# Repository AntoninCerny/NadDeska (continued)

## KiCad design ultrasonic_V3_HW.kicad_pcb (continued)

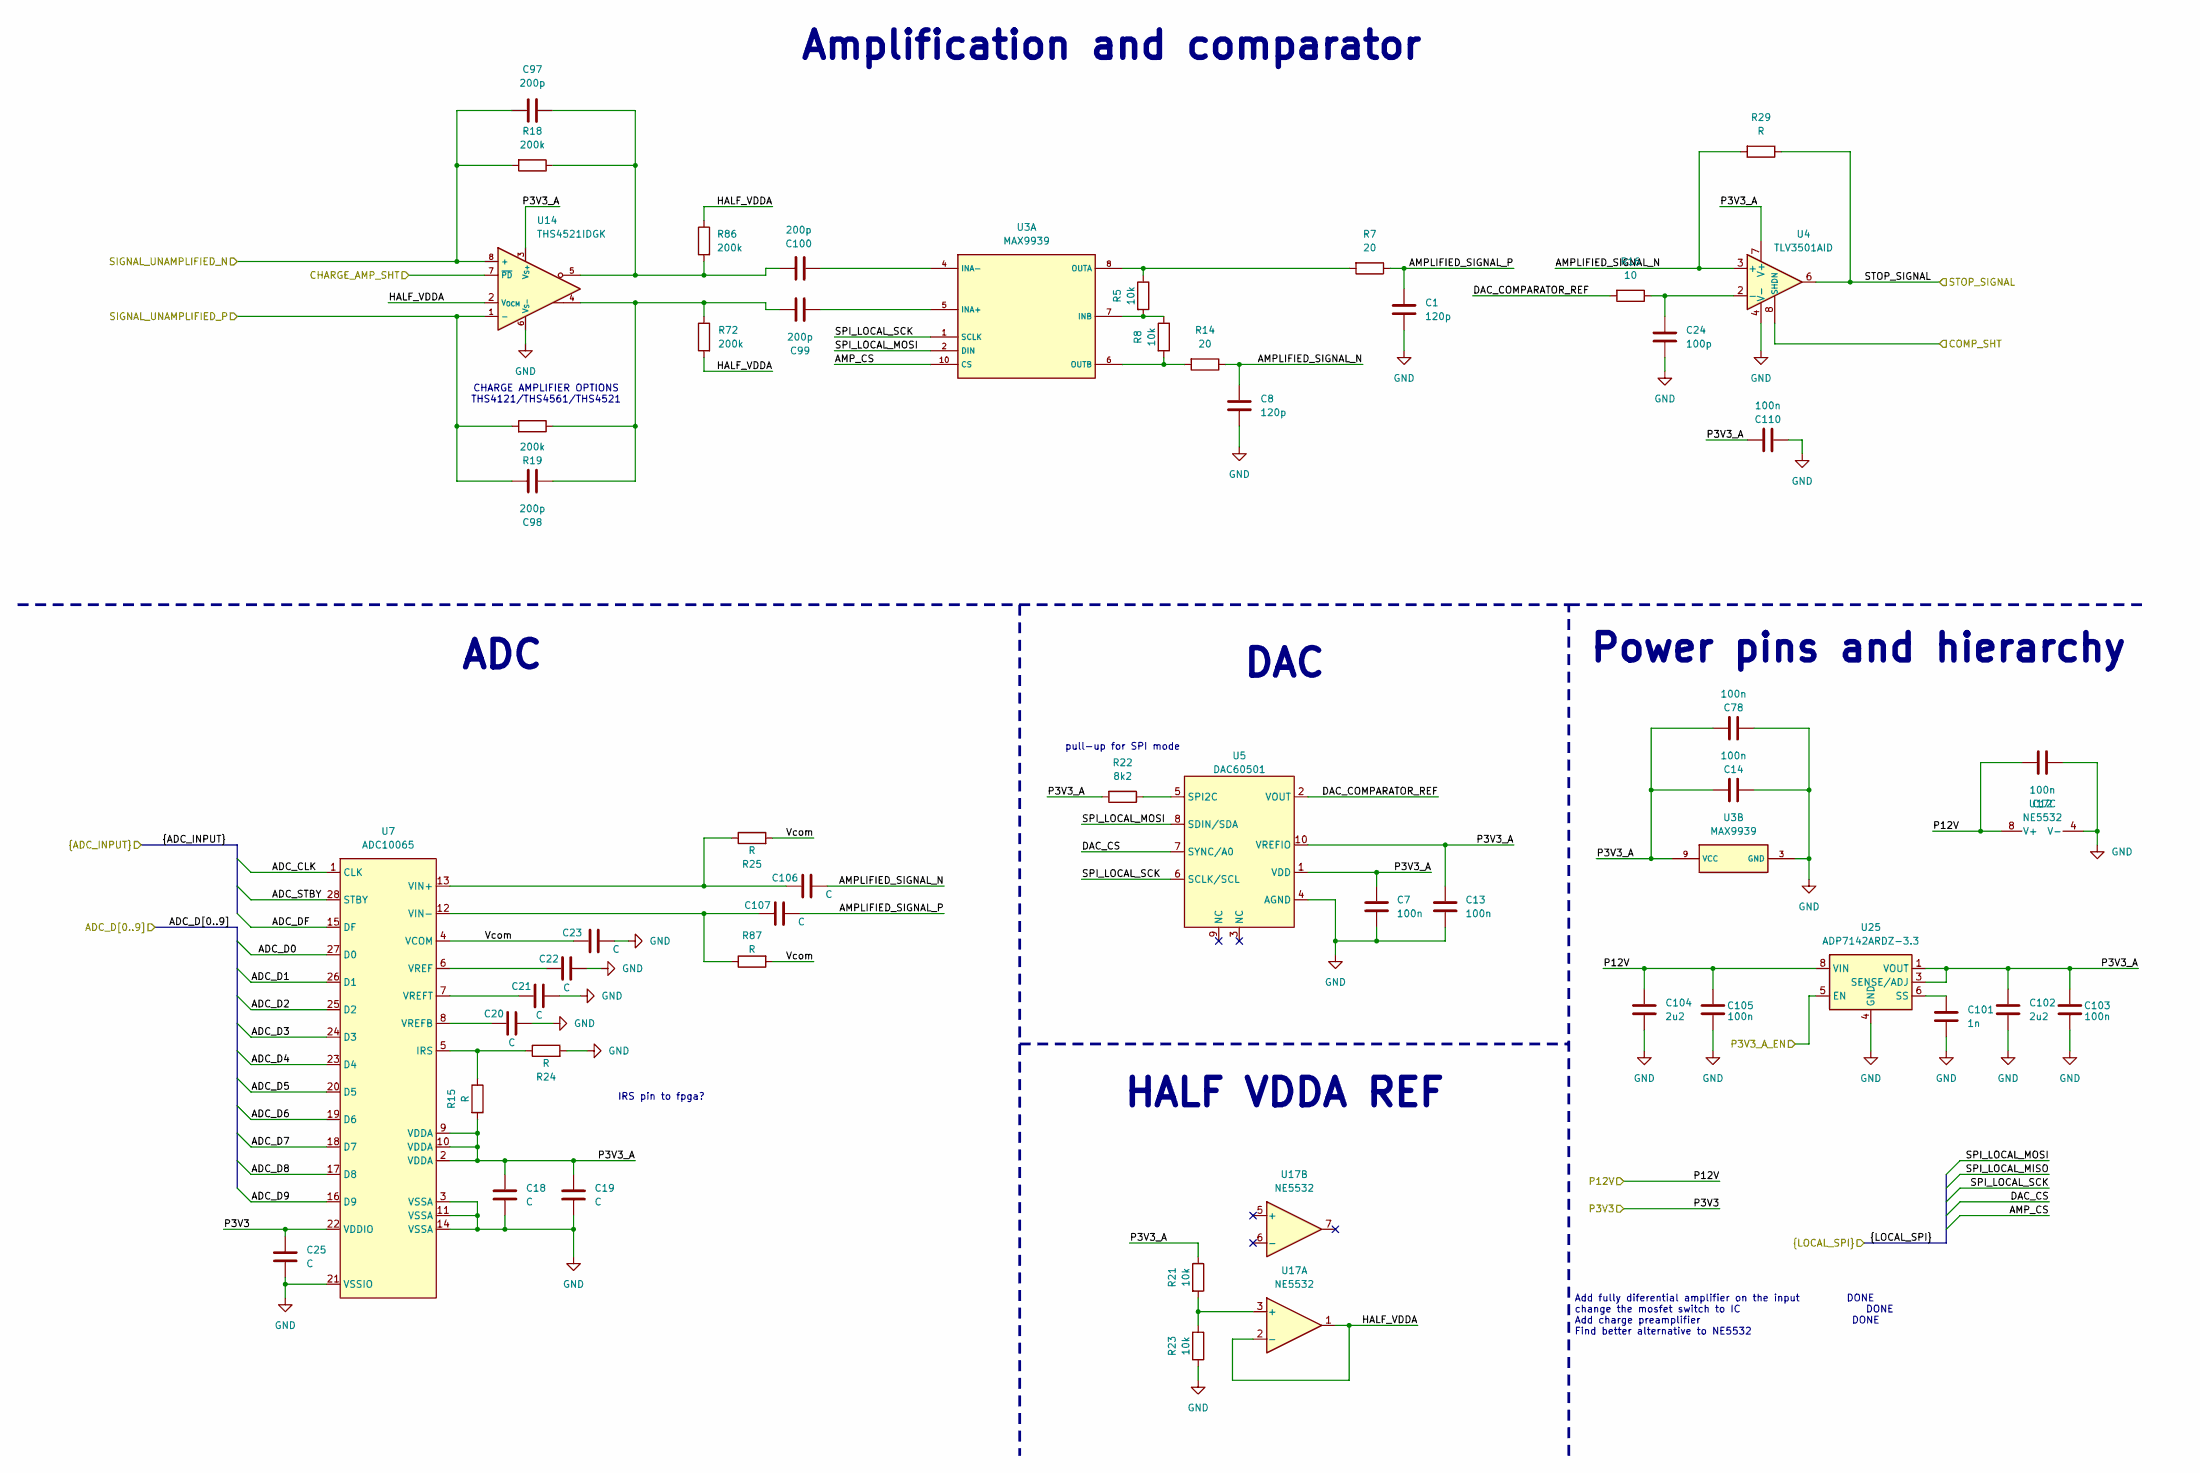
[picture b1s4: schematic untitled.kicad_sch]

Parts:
C1, C8: 120p; C_0603_1608Metric_Pad1.08x0.95mm_HandSolder
C7, C12, C13, C14, C78, C103, C105, C110: 100n; C_0603_1608Metric_Pad1.08x0.95mm_HandSolder
C18, C19, C20, C21, C22, C23, C25, C106, C107: C; C_0603_1608Metric_Pad1.08x0.95mm_HandSolder
C24: 100p; C_0603_1608Metric_Pad1.08x0.95mm_HandSolder
C97, C98, C99, C100: 200p; C_0603_1608Metric_Pad1.08x0.95mm_HandSolder
C101: 1n; C_0603_1608Metric_Pad1.08x0.95mm_HandSolder
C102, C104: 2u2; C_0805_2012Metric_Pad1.18x1.45mm_HandSolder
R5, R8, R21, R23: 10k; R_0603_1608Metric_Pad0.98x0.95mm_HandSolder
R7, R14: 20; R_0603_1608Metric_Pad0.98x0.95mm_HandSolder
R15, R24, R25, R29, R87: R; R_0603_1608Metric_Pad0.98x0.95mm_HandSolder
R16: 10; R_0603_1608Metric_Pad0.98x0.95mm_HandSolder
R18, R19, R72, R86: 200k; R_0603_1608Metric_Pad0.98x0.95mm_HandSolder
R22: 8k2; R_0603_1608Metric_Pad0.98x0.95mm_HandSolder
U3: MAX9939; uMAX 10 pin
U4: TLV3501AID; SOIC-8_3.9x4.9mm_P1.27mm
U5: DAC60501; VSSOP-10_3x3mm_P0.5mm
U7: ADC10065; TSSOP-28_4.4x9.7mm_P0.65mm
U14: THS4521IDGK; VSSOP-8_3.0x3.0mm_P0.65mm
U17: NE5532; SOIC-8_3.9x4.9mm_P1.27mm
U25: ADP7142ARDZ-3.3; SOIC-8-1EP_3.9x4.9mm_P1.27mm_EP2.29x3mm

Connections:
/ADC_CLK: U7.1 (CLK); also elsewhere on the board
/ADC_D0: U7.27 (D0); also elsewhere on the board
/ADC_D1: U7.26 (D1); also elsewhere on the board
/ADC_D2: U7.25 (D2); also elsewhere on the board
/ADC_D3: U7.24 (D3); also elsewhere on the board
/ADC_D4: U7.23 (D4); also elsewhere on the board
/ADC_D5: U7.20 (D5); also elsewhere on the board
/ADC_D6: U7.19 (D6); also elsewhere on the board
/ADC_D7: U7.18 (D7); also elsewhere on the board
/ADC_D8: U7.17 (D8); also elsewhere on the board
/ADC_D9: U7.16 (D9); also elsewhere on the board
/ADC_DF: U7.15 (DF); also elsewhere on the board
/ADC_STBY: U7.28 (STBY); also elsewhere on the board
/AMP_CS: U3.10 (CS); also elsewhere on the board
/AnalogFrontend/AMPLIFIED_SIGNAL_N: C8.2, C106.1, R14.1, R29.2, U4.3 (+)
/AnalogFrontend/AMPLIFIED_SIGNAL_P: C1.2, C107.1, R7.1
/AnalogFrontend/DAC_COMPARATOR_REF: R16.2, U5.2 (VOUT)
/AnalogFrontend/HALF_VDDA: R72.2, R86.1, U14.2 (V_{OCM}), U17.1, U17.2 (-)
/AnalogFrontend/P3V3_A: C7.2, C13.2, C14.1, C18.2, C19.2, C78.1, C102.2, C103.1, C110.1, R15.2, R21.1, R22.2, U3.9 (VCC), U4.7 (V+), U5.1 (VDD), U5.10 (VREFIO), U7.2 (VDDA), U7.9 (VDDA), U7.10 (VDDA), U14.3 (V_{S+}), U25.1 (VOUT), U25.2 (VOUT), U25.3 (SENSE/ADJ)
/AnalogFrontend/SIGNAL_UNAMPLIFIED_N: C97.2, R18.2, U14.8 (+); also elsewhere on the board
/AnalogFrontend/SIGNAL_UNAMPLIFIED_P: C98.2, R19.2, U14.1 (-); also elsewhere on the board
/AnalogFrontend/Vcom: C23.2, R25.2, R87.2, U7.4 (VCOM)
/CHARGE_AMP_SHT: U14.7 (~PD); also elsewhere on the board
/COMP_SHT: U4.8 (SHDN); also elsewhere on the board
/DAC_CS: U5.7 (SYNC/A0); also elsewhere on the board
/P3V3: C25.2, U7.22 (VDDIO); also elsewhere on the board
/P3V3_A_EN: U25.5 (EN); also elsewhere on the board
/P12V: C12.2, C104.2, C105.1, U17.8 (V+), U25.7 (VIN), U25.8 (VIN); also elsewhere on the board
/SPI_LOCAL_MOSI: U3.2 (DIN), U5.8 (SDIN/SDA); also elsewhere on the board
/SPI_LOCAL_SCK: U3.1 (SCLK), U5.6 (SCLK/SCL); also elsewhere on the board
/STOP_SIGNAL: R29.1, U4.6; also elsewhere on the board
GND: C1.1, C7.1, C8.1, C12.1, C13.1, C14.2, C18.1, C19.1, C20.1, C21.1, C22.1, C23.1, C24.1, C25.1, C78.2, C101.1, C102.1, C103.2, C104.1, C105.2, C110.2, R23.2, R24.2, U3.3 (GND), U4.4 (V-), U5.4 (AGND), U7.3 (VSSA), U7.11 (VSSA), U7.14 (VSSA), U7.21 (VSSIO), U14.6 (V_{S-}), U17.4 (V-), U25.4 (GND), U25.9 (GND); also elsewhere on the board
unnamed: C98.1, C99.2, R19.1, R72.1, U14.4
unnamed: C97.1, C100.2, R18.1, R86.2, U14.5
unnamed: C99.1, U3.5 (INA+)
unnamed: C100.1, U3.4 (INA-)
unnamed: R5.2, R8.1, U3.7 (INB)
unnamed: R5.1, R7.2, U3.8 (OUTA)
unnamed: R8.2, R14.2, U3.6 (OUTB)
unnamed: C24.2, R16.1, U4.2 (-)
unnamed: R22.1, U5.5 (SPI2C)
unnamed: R15.1, R24.1, U7.5 (IRS)
unnamed: C106.2, R25.1, U7.13 (VIN+)
unnamed: C107.2, R87.1, U7.12 (VIN-)
unnamed: C22.2, U7.6 (VREF)
unnamed: C20.2, U7.8 (VREFB)
unnamed: C21.2, U7.7 (VREFT)
unnamed: R21.2, R23.1, U17.3 (+)
unnamed: C101.2, U25.6 (SS)

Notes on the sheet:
HALF VDDA REF
pull-up for SPI mode
IRS pin to fpga?
Amplification and comparator
DAC
ADC
CHARGE AMPLIFIER OPTIONS THS4121/THS4561/THS4521
Power pins and hierarchy
Add fully diferential amplifier on the input DONE change the mosfet switch to IC DONE Add charge preamplifier DONE Find better alternative to NE5532

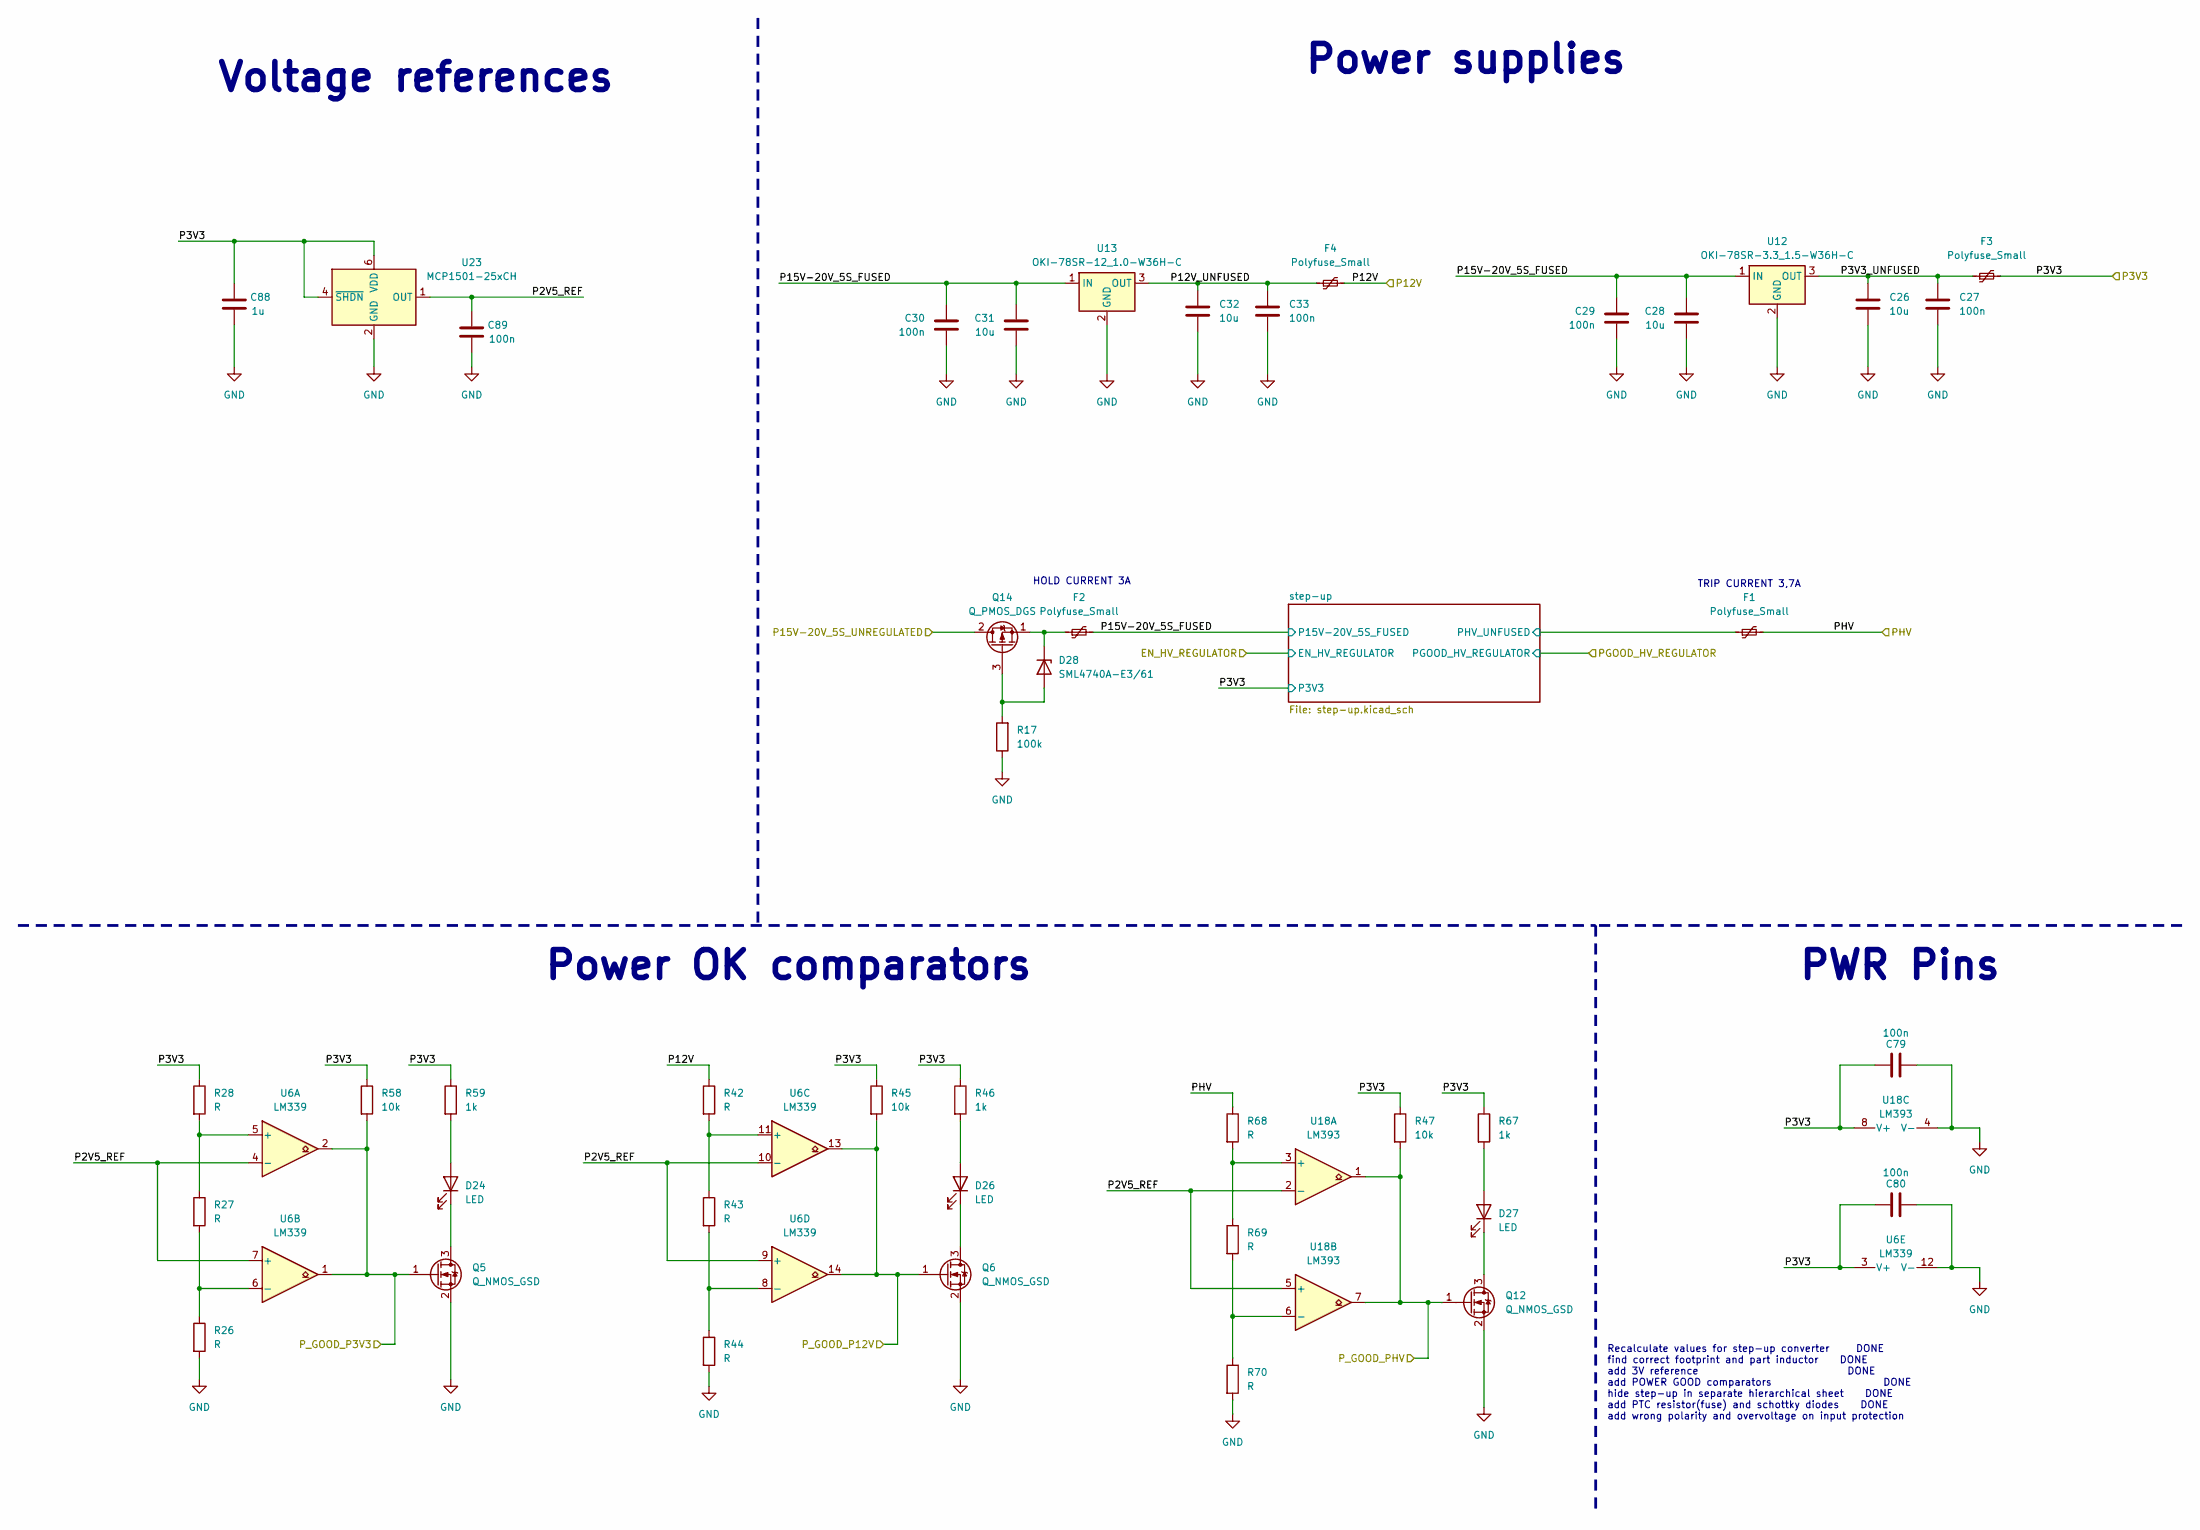
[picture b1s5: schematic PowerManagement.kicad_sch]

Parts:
C26, C28, C31, C32: 10u; C_0805_2012Metric_Pad1.18x1.45mm_HandSolder
C27, C29, C30, C33, C79, C80, C89: 100n; C_0603_1608Metric_Pad1.08x0.95mm_HandSolder
C88: 1u; C_0805_2012Metric_Pad1.18x1.45mm_HandSolder
D24, D26, D27: LED; LED_0805_2012Metric_Pad1.15x1.40mm_HandSolder
D28: SML4740A-E3/61; D_SMA_Handsoldering
F1, F2: Polyfuse_Small; Fuse_2920_7451Metric
F3, F4: Polyfuse_Small; Fuse_1206_3216Metric
Q5, Q6, Q12: Q_NMOS_GSD; SOT-23_Handsoldering
Q14: Q_PMOS_DGS; SOT-223-3_TabPin2
R17: 100k; R_1206_3216Metric_Pad1.30x1.75mm_HandSolder
R26, R27, R28, R42, R43, R44, R68, R69, R70: R; R_0603_1608Metric_Pad0.98x0.95mm_HandSolder
R45, R47, R58: 10k; R_0603_1608Metric_Pad0.98x0.95mm_HandSolder
R46, R59, R67: 1k; R_0603_1608Metric_Pad0.98x0.95mm_HandSolder
U6: LM339; TSSOP-14_4.4x5mm_P0.65mm
U12: OKI-78SR-3.3_1.5-W36H-C; Converter_DCDC_Murata_OKI-78SR_Horizontal
U13: OKI-78SR-12_1.0-W36H-C; Converter_DCDC_Murata_OKI-78SR_Horizontal
U18: LM393; TSSOP-8_4.4x3mm_P0.65mm
U23: MCP1501-25xCH; SOT-23-6

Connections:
/P3V3: C79.1, C80.1, C88.1, F3.2, R28.1, R45.1, R46.1, R47.1, R58.1, R59.1, R67.1, U6.3 (V+), U18.8 (V+), U23.4 (~SHDN), U23.6 (VDD); also elsewhere on the board
/P12V: F4.2, R42.1; also elsewhere on the board
/PHV: F1.2, R68.1; also elsewhere on the board
/P_GOOD_P3V3: Q5.1 (G), R58.2, U6.1, U6.2; also elsewhere on the board
/P_GOOD_P12V: Q6.1 (G), R45.2, U6.13, U6.14; also elsewhere on the board
/P_GOOD_PHV: Q12.1 (G), R47.2, U18.1, U18.7; also elsewhere on the board
/PowerManagement/P2V5_REF: C89.1, U6.4 (-), U6.7 (+), U6.9 (+), U6.10 (-), U18.2 (-), U18.5 (+), U23.1 (OUT)
/PowerManagement/P3V3_UNFUSED: C26.2, C27.1, F3.1, U12.3 (OUT)
/PowerManagement/P12V_UNFUSED: C32.2, C33.1, F4.1, U13.3 (OUT)
/PowerManagement/P15V-20V_5S_FUSED: C28.2, C29.1, C30.1, C31.2, F2.2, U12.1 (IN), U13.1 (IN); also elsewhere on the board
/PowerManagement/P15V-20V_5S_UNREGULATED: Q14.2 (D); also elsewhere on the board
/PowerManagement/step-up/PHV_UNFUSED: F1.1; also elsewhere on the board
GND: C26.1, C27.2, C28.1, C29.2, C30.2, C31.1, C32.1, C33.2, C79.2, C80.2, C88.2, C89.2, Q5.2 (S), Q6.2 (S), Q12.2 (S), R17.1, R26.2, R44.2, R70.2, U6.12 (V-), U12.2 (GND), U13.2 (GND), U18.4 (V-), U23.2 (GND), U23.3 (GND), U23.5 (GND); also elsewhere on the board
unnamed: D24.2 (A), R59.2
unnamed: D24.1 (K), Q5.3 (D)
unnamed: D26.2 (A), R46.2
unnamed: D26.1 (K), Q6.3 (D)
unnamed: D27.2 (A), R67.2
unnamed: D27.1 (K), Q12.3 (D)
unnamed: D28.2 (A), Q14.3 (G), R17.2
unnamed: D28.1 (K), F2.1, Q14.1 (S)
unnamed: R27.1, R28.2, U6.5 (+)
unnamed: R26.1, R27.2, U6.6 (-)
unnamed: R42.2, R43.1, U6.11 (+)
unnamed: R43.2, R44.1, U6.8 (-)
unnamed: R68.2, R69.1, U18.3 (+)
unnamed: R69.2, R70.1, U18.6 (-)

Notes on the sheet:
Recalculate values for step-up converter DONE find correct footprint and part inductor DONE add 3V reference DONE add POWER GOOD comparators DONE hide step-up in separate hierarchical sheet DONE add PTC resistor(fuse) and schottky diodes DONE add wrong polarity and overvoltage on input protection
TRIP CURRENT 3,7A
Voltage references
Power supplies
PWR Pins
HOLD CURRENT 3A
Power OK comparators

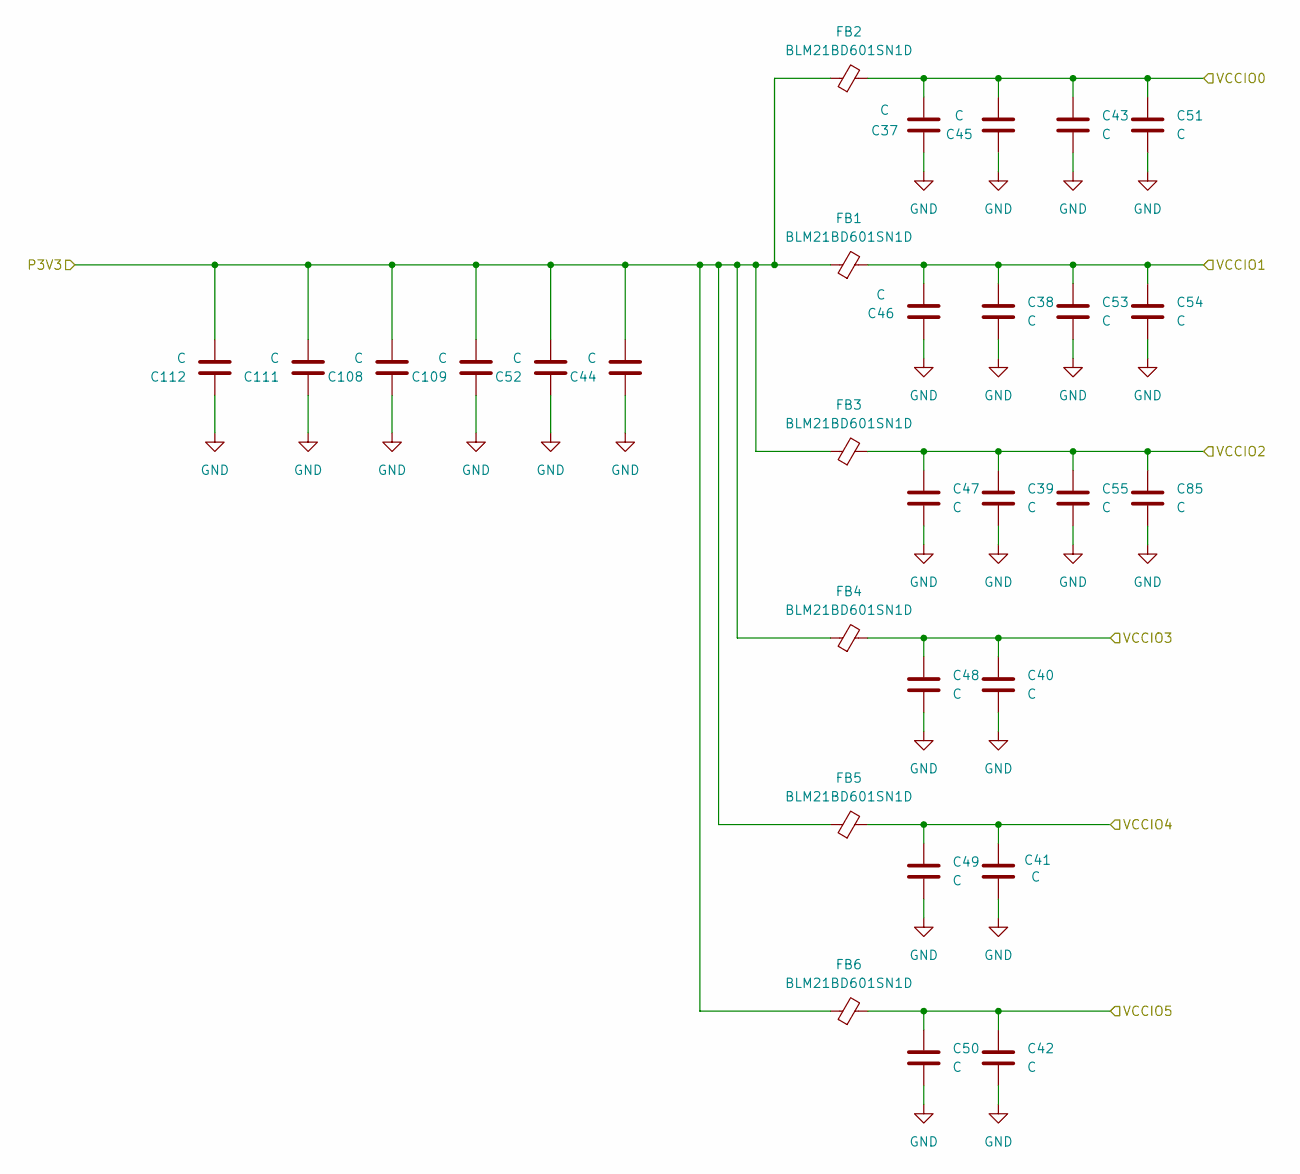
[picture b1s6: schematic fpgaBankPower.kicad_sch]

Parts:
C37, C38, C39, C40, C41, C42, C43, C45, C46, C47, C48, C49, C50, C51, C52, C53, C54, C55, C85, C108, C111, C112: C; C_0603_1608Metric_Pad1.08x0.95mm_HandSolder
C44, C109: C; C_0805_2012Metric_Pad1.18x1.45mm_HandSolder
FB1, FB2, FB3, FB4, FB5, FB6: BLM21BD601SN1D; R_0805_2012Metric_Pad1.20x1.40mm_HandSolder

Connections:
/P3V3: C44.1, C52.1, C108.1, C109.1, C111.1, C112.1, FB1.1, FB2.1, FB3.1, FB4.1, FB5.1, FB6.1; also elsewhere on the board
/fpga/fpgaBankPower/VCCIO0: C37.2, C43.1, C45.2, C51.1, FB2.2; also elsewhere on the board
/fpga/fpgaBankPower/VCCIO1: C38.1, C46.1, C53.1, C54.1, FB1.2; also elsewhere on the board
/fpga/fpgaBankPower/VCCIO2: C39.1, C47.1, C55.1, C85.1, FB3.2; also elsewhere on the board
/fpga/fpgaBankPower/VCCIO3: C40.1, C48.1, FB4.2; also elsewhere on the board
/fpga/fpgaBankPower/VCCIO4: C41.2, C49.1, FB5.2; also elsewhere on the board
/fpga/fpgaBankPower/VCCIO5: C42.1, C50.1, FB6.2; also elsewhere on the board
GND: C37.1, C38.2, C39.2, C40.2, C41.1, C42.2, C43.2, C44.2, C45.1, C46.2, C47.2, C48.2, C49.2, C50.2, C51.2, C52.2, C53.2, C54.2, C55.2, C85.2, C108.2, C109.2, C111.2, C112.2; also elsewhere on the board

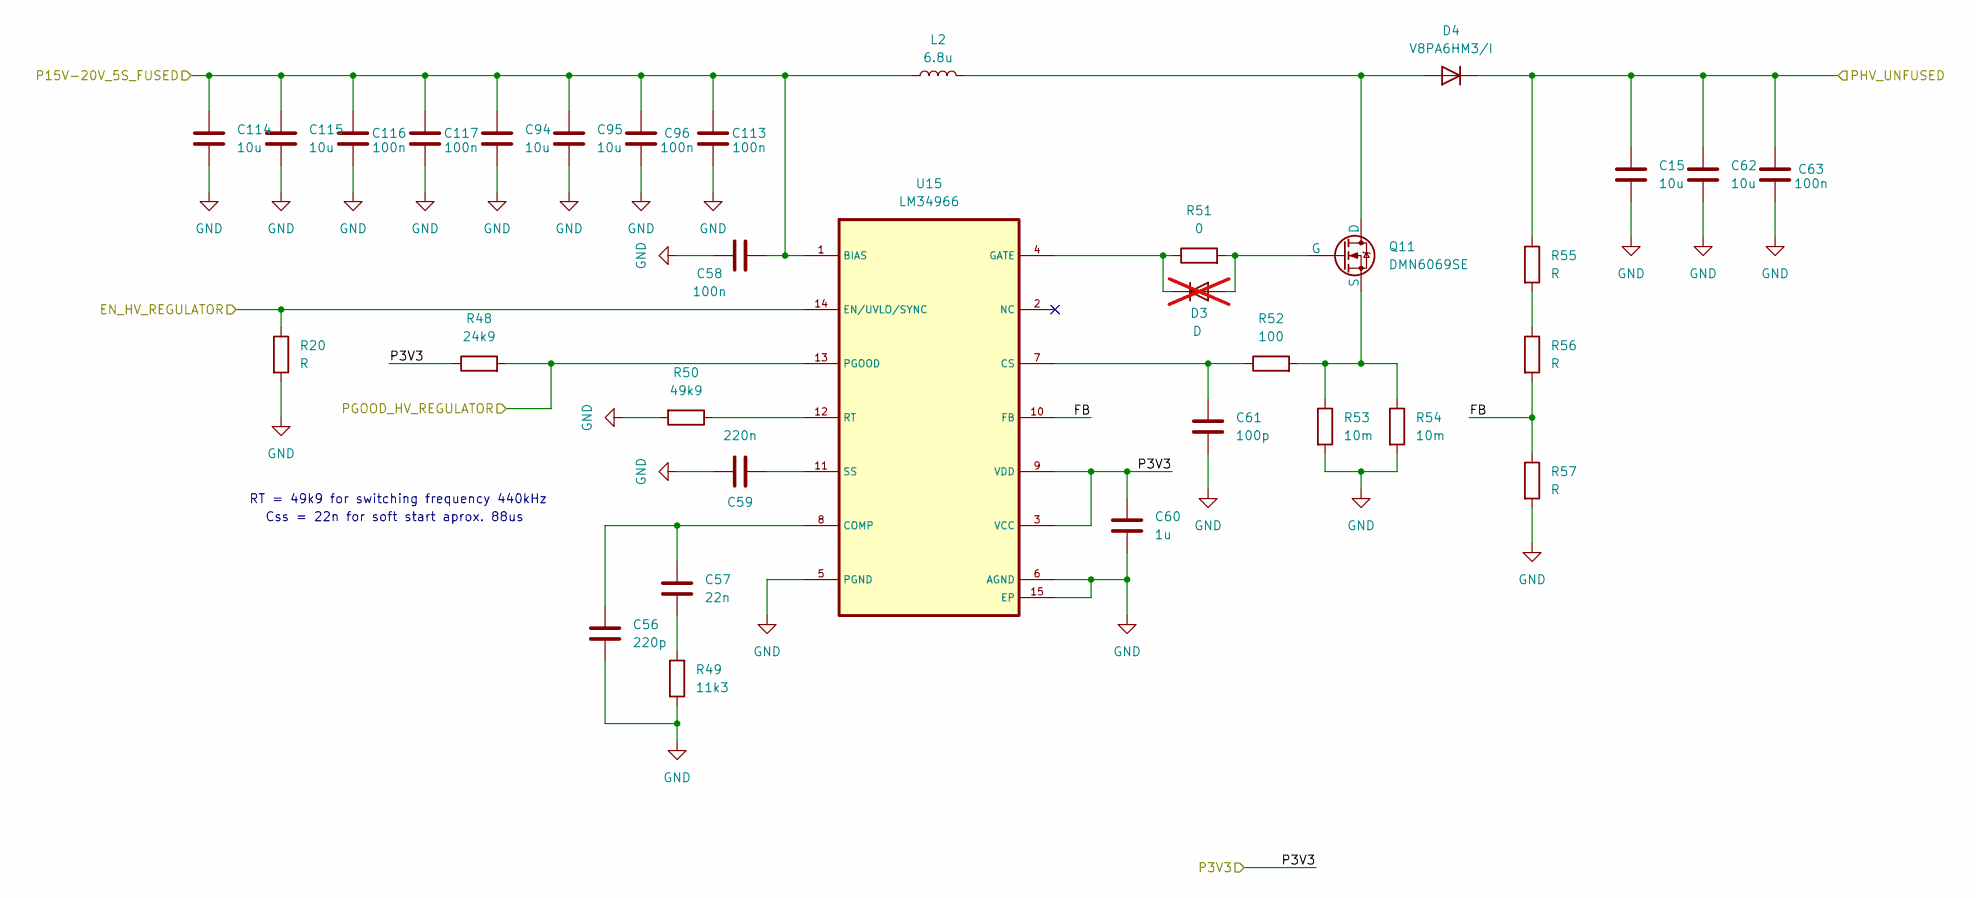
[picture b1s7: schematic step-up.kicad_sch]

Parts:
C15, C62, C94, C95, C114, C115: 10u; C_0805_2012Metric_Pad1.18x1.45mm_HandSolder
C56: 220p; C_0603_1608Metric_Pad1.08x0.95mm_HandSolder
C57: 22n; C_0603_1608Metric_Pad1.08x0.95mm_HandSolder
C58, C63, C96, C113, C116, C117: 100n; C_0603_1608Metric_Pad1.08x0.95mm_HandSolder
C59: 220n; C_0603_1608Metric_Pad1.08x0.95mm_HandSolder
C60: 1u; C_0805_2012Metric_Pad1.18x1.45mm_HandSolder
C61: 100p; C_0603_1608Metric_Pad1.08x0.95mm_HandSolder
D3: D; D_SOD-123; not fitted
D4: V8PA6HM3/I; Vishay_SMPA
L2: 6.8u; L_Bourns-SRN8040_8x8.15mm
Q11: DMN6069SE; SOT-223-3_TabPin2
R20, R55, R56, R57: R; R_0603_1608Metric_Pad0.98x0.95mm_HandSolder
R48: 24k9; R_0603_1608Metric_Pad0.98x0.95mm_HandSolder
R49: 11k3; C_0603_1608Metric_Pad1.08x0.95mm_HandSolder
R50: 49k9; R_0603_1608Metric_Pad0.98x0.95mm_HandSolder
R51: 0; R_0603_1608Metric_Pad0.98x0.95mm_HandSolder
R52: 100; R_0603_1608Metric_Pad0.98x0.95mm_HandSolder
R53, R54: 10m; R_0603_1608Metric_Pad0.98x0.95mm_HandSolder
U15: LM34966; HTSSOP-14-1EP_4.4x5mm_P0.65mm_EP3.4x5mm_Mask3x3.1mm_Thermal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

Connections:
/EN_HV_REGULATOR: R20.1, U15.14 (EN/UVLO/SYNC); also elsewhere on the board
/P3V3: C60.2, R48.1, U15.3 (VCC), U15.9 (VDD); also elsewhere on the board
/PowerManagement/P15V-20V_5S_FUSED: C58.1, C94.2, C95.2, C96.1, C113.1, C114.2, C115.2, C116.1, C117.1, L2.1, U15.1 (BIAS); also elsewhere on the board
/PowerManagement/step-up/FB: R56.2, R57.1, U15.10 (FB)
/PowerManagement/step-up/PHV_UNFUSED: C15.2, C62.2, C63.1, D4.1 (K), R55.1; also elsewhere on the board
/fpga/PGOOD_HV_REGULATOR: R48.2, U15.13 (PGOOD); also elsewhere on the board
GND: C15.1, C56.1, C58.2, C59.2, C60.1, C61.2, C62.1, C63.2, C94.1, C95.1, C96.2, C113.2, C114.1, C115.1, C116.2, C117.2, R20.2, R49.1, R50.2, R53.2, R54.2, R57.2, U15.5 (PGND), U15.6 (AGND), U15.15 (EP); also elsewhere on the board
unnamed: C57.1, R49.2
unnamed: D3.2 (A), Q11.1 (G), R51.2
unnamed: D3.1 (K), R51.1, U15.4 (GATE)
unnamed: D4.2 (A), L2.2, Q11.2 (D)
unnamed: Q11.3 (S), R52.2, R53.1, R54.1
unnamed: R55.2, R56.1
unnamed: C56.2, C57.2, U15.8 (COMP)
unnamed: C61.1, R52.1, U15.7 (CS)
unnamed: R50.1, U15.12 (RT)
unnamed: C59.1, U15.11 (SS)

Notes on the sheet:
Css = 22n for soft start aprox. 88us
RT = 49k9 for switching frequency 440kHz

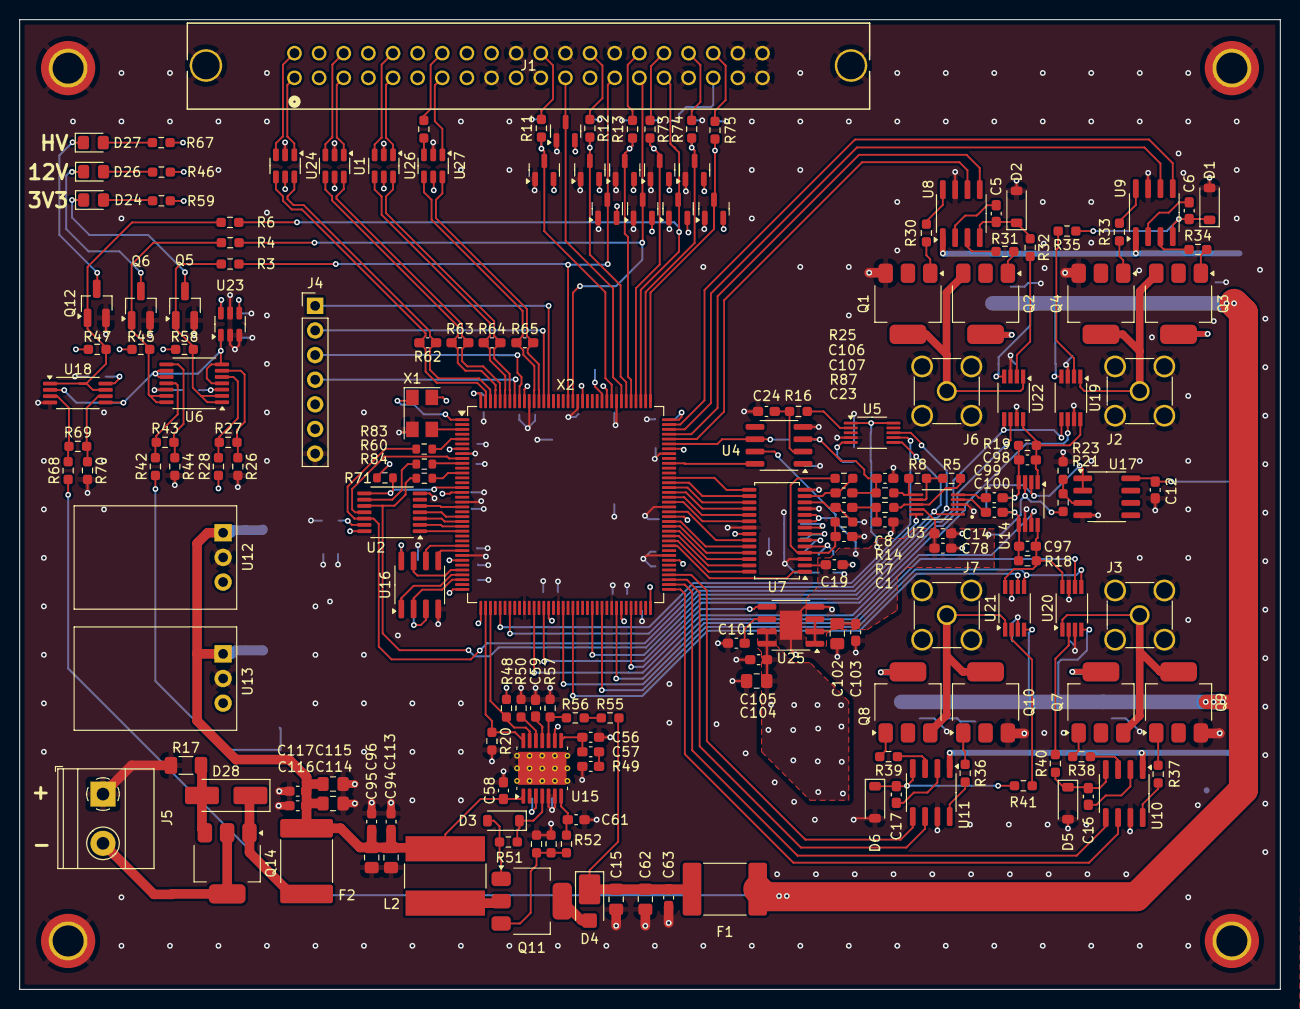
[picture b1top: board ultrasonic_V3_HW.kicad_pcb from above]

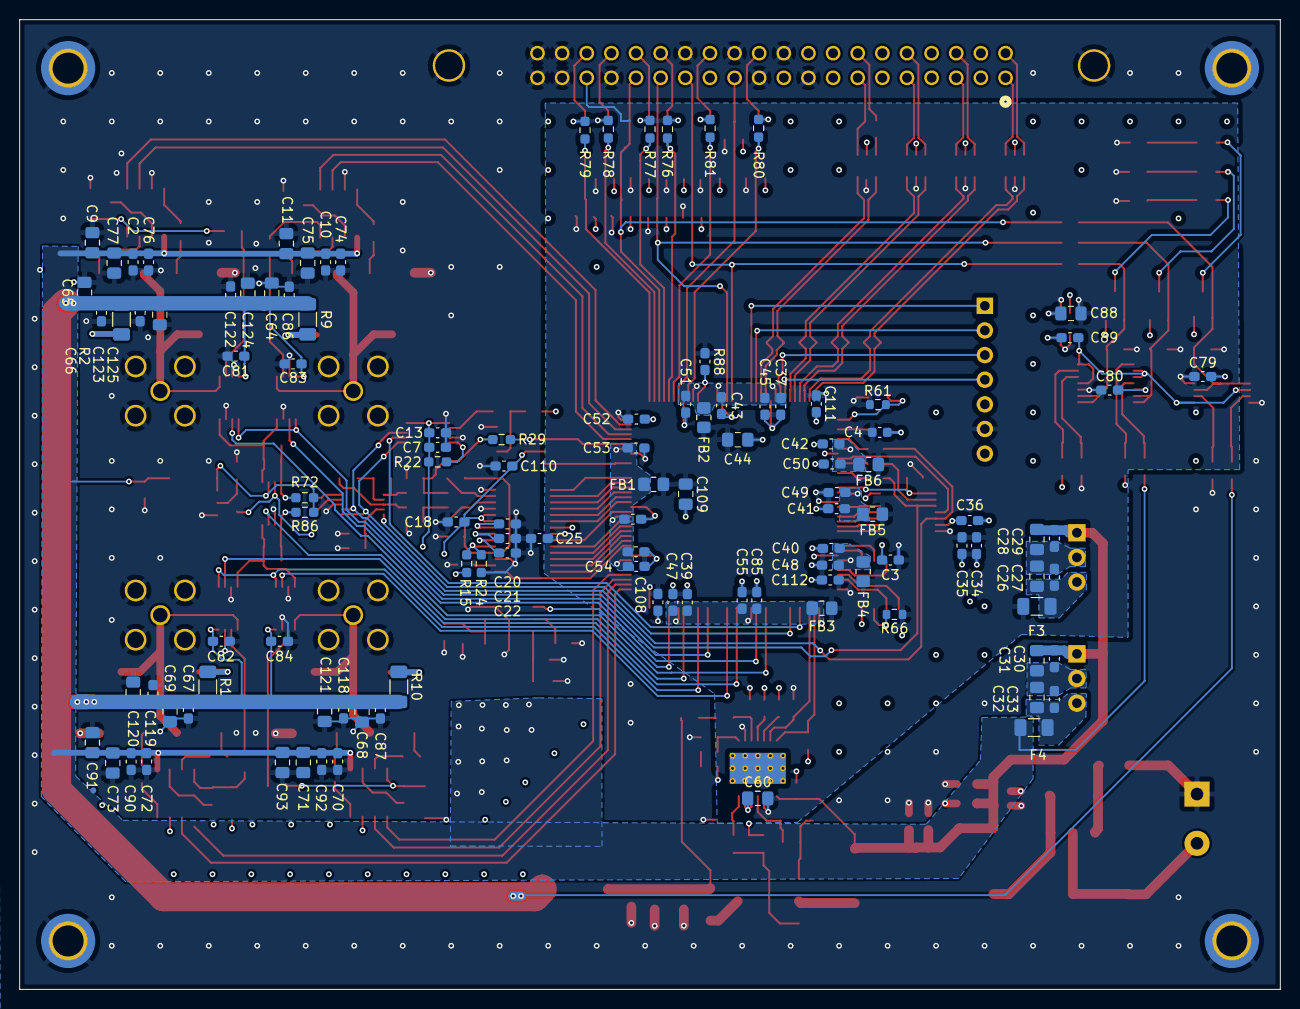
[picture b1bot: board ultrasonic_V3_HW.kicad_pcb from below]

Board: 4 copper layers, 130.0 x 100.0 mm, 296 parts (113 on the bottom side), 200 nets.

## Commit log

2024-09-10 Analog front end sorted
2024-09-25 schematics done
2024-09-29 ready schematic for layout
2024-09-29 new analog front end
2024-10-01 schematic ready, basic layout done
2024-10-01 changed pins on fpga
2024-10-04 before changing MUX
2024-10-12 no errors schematic, basic routing done
2024-10-23 DONE - before checking
2024-10-27 most values in schematic filled corrected footprint mistake
2024-11-08 V1 completed, starting on V2 after consultation with mr. Chalupa
2024-11-26 V2 finished
